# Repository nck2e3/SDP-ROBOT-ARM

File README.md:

# Face Tracking Robotic Arm

## Overview

This repository documents a Senior Design Project (SDP) centered around a robotic arm system. The project features **custom-developed firmware and hardware**, built to extend and optimize the functionality of an existing mechanical design. The full technical report can be found in the `Docs/` folder of this repository. This project was developed by **Junhee Lee** and **Noah King** as part of their Senior Design Project.

> ⚠️ Note: The mechanical CAD files—except for our custom-modeled housing—are sourced directly from the original forked repository, community_robot_arm, and remain unmodified. All electronic hardware and firmware in this repository are original to this project.

| Schematic                        |
|----------------------------------|
|        |

| PCB Photo                        |
|----------------------------------|
|        |

| Custom Housing                   | Entire Assembly                  |
|----------------------------------|----------------------------------|
|      |          |

## Repository Structure

- `Firmware/` - Custom embedded firmware developed for motor control, sensing, and task coordination.
- `Hardware/` - Custom PCB schematics and layouts designed to interface with the robotic arm and support sensors and actuators.
- `Mechanical_Design/` - Original CAD files sourced from the forked project (see Acknowledgments).
- `Documentation/` - Design notes, test procedures, and system configuration details.

## Key Features

- Custom PCB design utilizing TMC-2209 motor drivers and an STM-32 microcontroller
- Face detection and tracking via external vision processing pipeline

## Acknowledgments

All firmware, hardware integration, and system-level enhancements were designed and implemented by the team.

Mechanical design elements, including all CAD files, originate from the [community_robot_arm](https://github.com/20sffactory/community_robot_arm) repository. These files were used unmodified and served as the foundation for the custom developments described in this repository.

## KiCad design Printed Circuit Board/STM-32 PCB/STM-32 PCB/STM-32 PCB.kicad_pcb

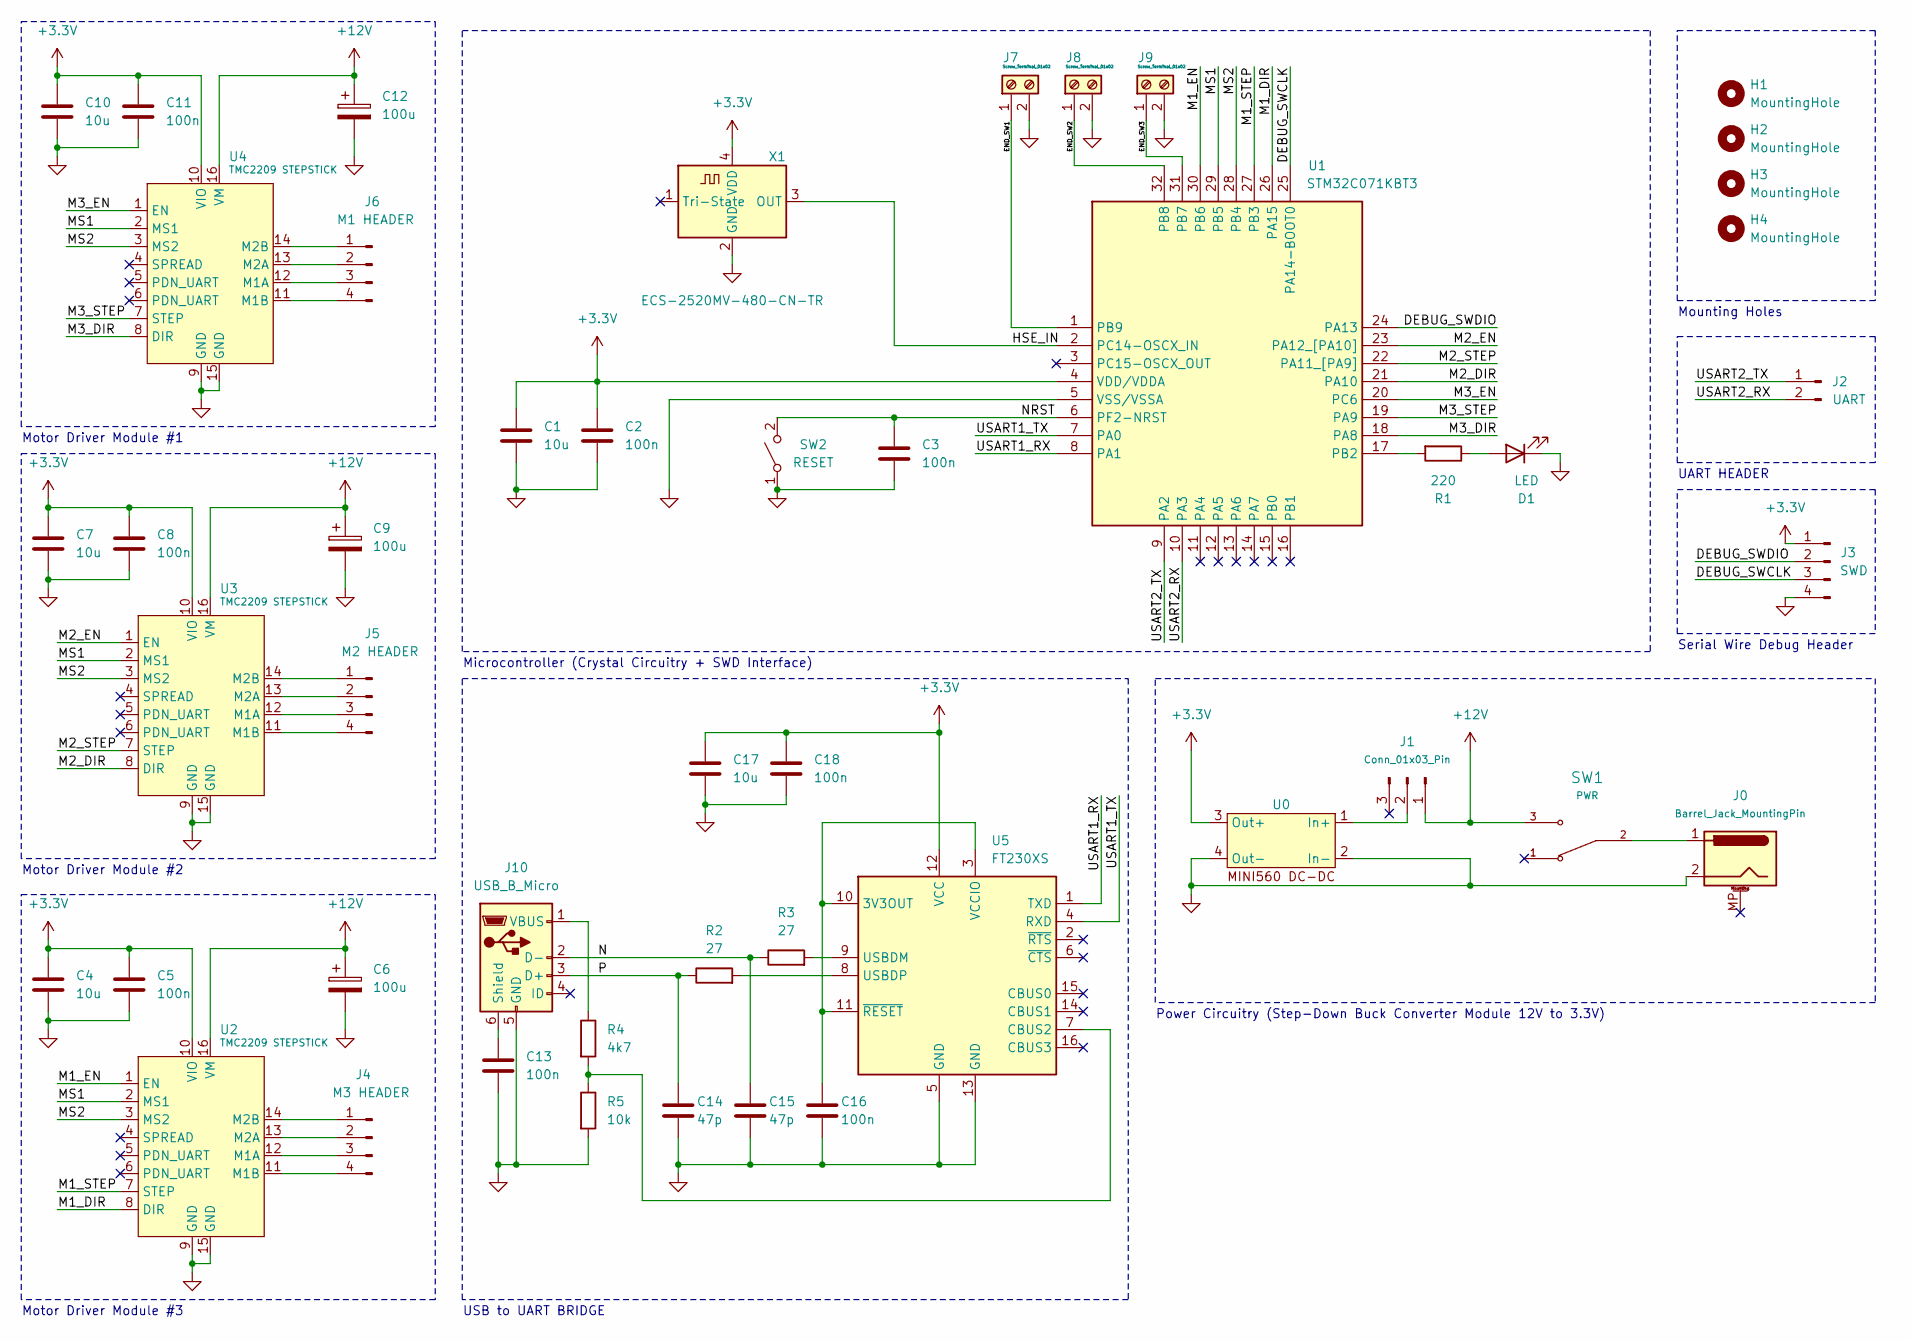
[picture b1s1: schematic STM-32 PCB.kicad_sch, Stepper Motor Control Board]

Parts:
C1, C4, C7, C10, C17: 10u; C_1206_3216Metric_Pad1.33x1.80mm_HandSolder
C2, C3, C5, C8, C11, C13, C16, C18: 100n; C_0603_1608Metric
C6, C9, C12: 100u; 50YXJ100MT78X11.5
C14, C15: 47p; C_0603_1608Metric
D1: LED; LED_1206_3216Metric
H1, H2, H3, H4: MountingHole; MountingHole_3.2mm_M3
J0: Barrel_Jack_MountingPin; BarrelJack_Horizontal
J1: Conn_01x03_Pin; PinHeader_1x03_P2.54mm_Vertical
J2: UART; PinHeader_1x02_P2.54mm_Vertical
J3: SWD; PinHeader_1x04_P2.54mm_Vertical
J4: M3 HEADER; PinHeader_1x04_P2.54mm_Vertical
J5: M2 HEADER; PinHeader_1x04_P2.54mm_Vertical
J6: M1 HEADER; PinHeader_1x04_P2.54mm_Vertical
J7, J8, J9: Screw_Terminal_01x02; TerminalBlock_Phoenix_MPT-0,5-2-2.54_1x02_P2.54mm_Horizontal
J10: USB_B_Micro; USB_Micro-B_Amphenol_10118193-0001LF_Horizontal
R1: 220; R_0603_1608Metric
R2, R3: 27; R_0603_1608Metric
R4: 4k7; R_0603_1608Metric
R5: 10k; R_0603_1608Metric
SW1: PWR; SW_500SSP1S1M6QEA; PARTREV D
SW2: RESET; SW_TH_Tactile_Omron_B3F-10xx
U0: MINI-560 DC-DC; MINI-560
U1: STM32C071KBT3; QFP80P900X900X160-32N; Manufacturer_Part_Number STM32C071KBT3
U2, U3, U4: TMC2209 STEPSTICK; TMC-2209_Stepstick
U5: FT230XS; SSOP-16_3.9x4.9mm_P0.635mm
X1: ECS-2520MV-480-CN-TR; Oscillator_SMD_ECS_2520MV-xxx-xx-4Pin_2.5x2.0mm

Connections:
+3.3V: C1.1, C2.1, C4.1, C5.1, C7.1, C8.1, C10.1, C11.1, C17.1, C18.1, J3.1, U0.3 (Out+), U1.4 (VDD/VDDA), U2.10 (VIO), U3.10 (VIO), U4.10 (VIO), U5.12 (VCC), X1.4 (VDD)
+12V: C6.1, C9.1, C12.1, J1.1, SW1.3, U2.16 (VM), U3.16 (VM), U4.16 (VM)
/DEBUG_SWCLK: J3.3, U1.25 (PA14-BOOT0)
/DEBUG_SWDIO: J3.2, U1.24 (PA13)
/END_SW1: J7.1, U1.1 (PB9)
/END_SW2: J8.1, U1.32 (PB8)
/END_SW3: J9.1, U1.31 (PB7)
/HSE_IN: U1.2 (PC14-OSCX_IN), X1.3 (OUT)
/M1_DIR: U1.26 (PA15), U2.8 (DIR)
/M1_EN: U1.30 (PB6), U2.1 (EN)
/M1_STEP: U1.27 (PB3), U2.7 (STEP)
/M2_DIR: U1.21 (PA10), U3.8 (DIR)
/M2_EN: U1.23 (PA12_[PA10]), U3.1 (EN)
/M2_STEP: U1.22 (PA11_[PA9]), U3.7 (STEP)
/M3_DIR: U1.18 (PA8), U4.8 (DIR)
/M3_EN: U1.20 (PC6), U4.1 (EN)
/M3_STEP: U1.19 (PA9), U4.7 (STEP)
/MS1: U1.29 (PB5), U2.2 (MS1), U3.2 (MS1), U4.2 (MS1)
/MS2: U1.28 (PB4), U2.3 (MS2), U3.3 (MS2), U4.3 (MS2)
/N: C15.1, J10.2 (D-), R3.1
/NRST: C3.1, SW2.2 (B), U1.6 (PF2-NRST)
/P: C14.1, J10.3 (D+), R2.1
/USART1_RX: U1.8 (PA1), U5.1 (TXD)
/USART1_TX: U1.7 (PA0), U5.4 (RXD)
/USART2_RX: J2.2, U1.10 (PA3)
/USART2_TX: J2.1, U1.9 (PA2)
GND: C1.2, C2.2, C3.2, C4.2, C5.2, C6.2, C7.2, C8.2, C9.2, C10.2, C11.2, C12.2, C13.2, C14.2, C15.2, C16.2, C17.2, C18.2, D1.1 (K), J0.2, J3.4, J7.2, J8.2, J9.2, J10.5 (GND), R5.2, SW2.1 (A), U0.2 (In-), U0.4 (Out-), U1.5 (VSS/VSSA), U2.9 (GND), U2.15 (GND), U3.9 (GND), U3.15 (GND), U4.9 (GND), U4.15 (GND), U5.5 (GND), U5.13 (GND), X1.2 (GND)
unnamed: D1.2 (A), R1.1
unnamed: J0.1, SW1.2
unnamed: J1.2, U0.1 (In+)
unnamed: J4.1, U2.14 (M2B)
unnamed: J4.2, U2.13 (M2A)
unnamed: J4.3, U2.12 (M1A)
unnamed: J4.4, U2.11 (M1B)
unnamed: J5.1, U3.14 (M2B)
unnamed: J5.2, U3.13 (M2A)
unnamed: J5.3, U3.12 (M1A)
unnamed: J5.4, U3.11 (M1B)
unnamed: J6.1, U4.14 (M2B)
unnamed: J6.2, U4.13 (M2A)
unnamed: J6.3, U4.12 (M1A)
unnamed: J6.4, U4.11 (M1B)
unnamed: C13.1, J10.6 (Shield)
unnamed: J10.1 (VBUS), R4.1
unnamed: R1.2, U1.17 (PB2)
unnamed: C16.1, U5.3 (VCCIO), U5.10 (3V3OUT), U5.11 (~RESET)
unnamed: R4.2, R5.1, U5.7 (CBUS2)
unnamed: R3.2, U5.9 (USBDM)
unnamed: R2.2, U5.8 (USBDP)

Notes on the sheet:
Motor Driver Module #2
UART HEADER
Serial Wire Debug Header
Motor Driver Module #1
Power Circuitry (Step-Down Buck Converter Module 12V to 3.3V)
USB to UART BRIDGE
Mounting Holes
Microcontroller (Crystal Circuitry + SWD Interface)
Motor Driver Module #3

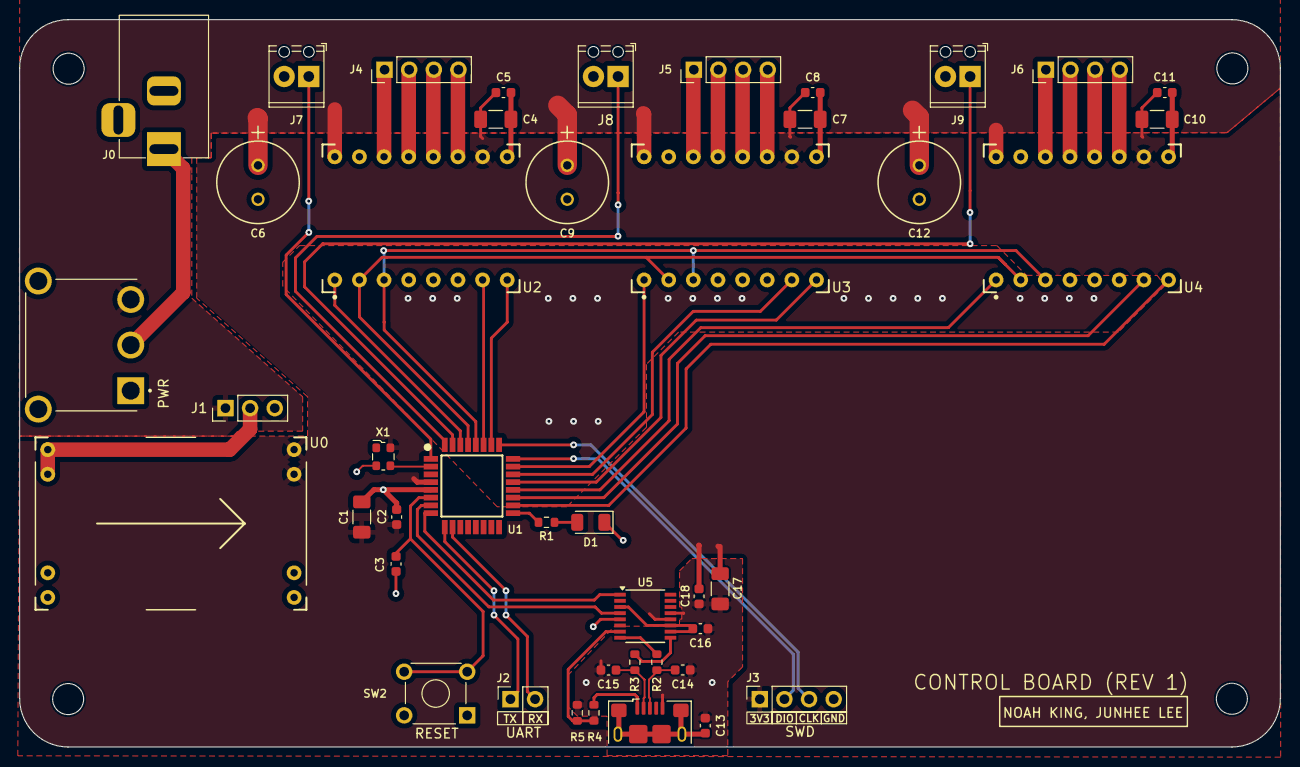
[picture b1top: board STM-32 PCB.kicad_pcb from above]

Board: 2 copper layers, 130.0 x 75.0 mm, 48 parts (0 on the bottom side), 49 nets.

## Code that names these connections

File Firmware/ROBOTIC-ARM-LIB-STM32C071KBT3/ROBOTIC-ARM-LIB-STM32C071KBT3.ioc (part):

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Mcu.Name=STM32C071KBTx
Mcu.Package=LQFP32_GP
Mcu.UserName=STM32C071KBTx
PA0.Mode=Asynchronous
PA0.Signal=USART1_TX
PA1.Mode=Asynchronous
PA1.Signal=USART1_RX
PA10\ [PA12].Signal=GPIO_Output
PA11\ [PA9].Signal=GPIO_Output
PA12\ [PA10].Signal=GPIO_Output
PA13.Mode=Serial_Wire
PA13.Signal=DEBUG_SWDIO
PA14-BOOT0.Mode=Serial_Wire
PA14-BOOT0.Signal=DEBUG_SWCLK
PA15.Signal=GPIO_Output
PA2.Mode=Asynchronous
PA2.Signal=USART2_TX
PA3.Mode=Asynchronous
PA3.Signal=USART2_RX
PA8.Signal=GPIO_Output
PA9\ [PA11].Signal=GPIO_Output
PB2.Signal=GPIO_Output
PB3.Signal=GPIO_Output
PB4.Signal=GPIO_Output
PB5.Signal=GPIO_Output
PB6.Signal=GPIO_Output
PB7.GPIOParameters=GPIO_PuPd
PB7.GPIO_PuPd=GPIO_PULLUP
PB7.Signal=GPIO_Input
PB8.GPIOParameters=GPIO_PuPd
PB8.GPIO_PuPd=GPIO_PULLUP
PB8.Signal=GPIO_Input
PB9.GPIOParameters=GPIO_PuPd
PB9.GPIO_PuPd=GPIO_PULLUP
PB9.Signal=GPIO_Input
PC14-OSCX_IN(PC14).Mode=HSE-External-Clock-Source
PC14-OSCX_IN(PC14).Signal=RCC_OSCX_IN
PC6.Signal=GPIO_Output
RCC.HSE_VALUE=48000000
RCC.SYSCLKFreq_VALUE=48000000
RCC.SYSCLKSource=RCC_SYSCLKSOURCE_HSIUSB48
board=custom

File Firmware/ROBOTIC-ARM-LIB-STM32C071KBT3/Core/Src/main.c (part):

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  /* USER CODE BEGIN 2 */
  HAL_TIM_Base_Start(&htim1);
  stepper_init(&M1_DRIVER,
			   M1_EN_PORT, M1_EN_PIN,
		       GLOBAL_MS1_PORT, GLOBAL_MS1_PIN,
			   GLOBAL_MS2_PORT, GLOBAL_MS2_PIN,
			   M1_STEP_PORT, M1_STEP_PIN,
			   M1_DIR_PORT, M1_DIR_PIN,
		       M2_ENDSTOP_PORT, M2_ENDSTOP_PIN);
  stepper_init(&M2_DRIVER,
		   	   M2_EN_PORT, M2_EN_PIN,
			   GLOBAL_MS1_PORT, GLOBAL_MS1_PIN,
			   GLOBAL_MS2_PORT, GLOBAL_MS2_PIN,
			   M2_STEP_PORT, M2_STEP_PIN,
			   M2_DIR_PORT, M2_DIR_PIN,
			   M2_ENDSTOP_PORT, M2_ENDSTOP_PIN);
  stepper_init(&M3_DRIVER,
		       M3_EN_PORT, M3_EN_PIN,
		       GLOBAL_MS1_PORT, GLOBAL_MS1_PIN,
		       GLOBAL_MS2_PORT, GLOBAL_MS2_PIN,
		       M3_STEP_PORT, M3_STEP_PIN,
		       M3_DIR_PORT, M3_DIR_PIN,
		       M3_ENDSTOP_PORT, M3_ENDSTOP_PIN);

  const char debug_msg[] = "STARTING UP!!!\n";
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  /*Configure GPIO pin Output Level */
  HAL_GPIO_WritePin(GPIOC, GPIO_PIN_6, GPIO_PIN_RESET);

  /*Configure GPIO pins : PB9 PB7 PB8 */
  GPIO_InitStruct.Pin = GPIO_PIN_9|GPIO_PIN_7|GPIO_PIN_8;
  GPIO_InitStruct.Mode = GPIO_MODE_INPUT;
  GPIO_InitStruct.Pull = GPIO_PULLUP;
  HAL_GPIO_Init(GPIOB, &GPIO_InitStruct);

  /*Configure GPIO pins : PB2 PB3 PB4 PB5
                           PB6 */
  GPIO_InitStruct.Pin = GPIO_PIN_2|GPIO_PIN_3|GPIO_PIN_4|GPIO_PIN_5
                          |GPIO_PIN_6;
  GPIO_InitStruct.Mode = GPIO_MODE_OUTPUT_PP;
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  GPIO_InitStruct.Speed = GPIO_SPEED_FREQ_LOW;
  HAL_GPIO_Init(GPIOB, &GPIO_InitStruct);

  /*Configure GPIO pins : PA8 PA9 PA10 PA11
                           PA12 PA15 */
  GPIO_InitStruct.Pin = GPIO_PIN_8|GPIO_PIN_9|GPIO_PIN_10|GPIO_PIN_11
                          |GPIO_PIN_12|GPIO_PIN_15;
  GPIO_InitStruct.Mode = GPIO_MODE_OUTPUT_PP;
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  GPIO_InitStruct.Speed = GPIO_SPEED_FREQ_LOW;
  HAL_GPIO_Init(GPIOA, &GPIO_InitStruct);

  /*Configure GPIO pin : PC6 */
  GPIO_InitStruct.Pin = GPIO_PIN_6;
  GPIO_InitStruct.Mode = GPIO_MODE_OUTPUT_PP;
  GPIO_InitStruct.Pull = GPIO_NOPULL;
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
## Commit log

2025-05-01 Removed firmware folders...
2025-05-01 Added custom firmware, added PCB files, added software, removed arduino firmware...
2025-05-01 Skeleton documentation...
2025-05-01 Updated documentation...
2025-05-27 Added images and more docs...
2025-05-27 Added more images and updated documentation...
2025-05-27 Updated directory structure...

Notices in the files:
Firmware/ROBOTIC-ARM-LIB-STM32C071KBT3/Core/Src/main.c:
Copyright (c) 2025 STMicroelectronics.
All rights reserved.
This software is licensed under terms that can be found in the LICENSE file
parts and their libraries:
Copyright 2016 Accelerated Designs. All rights reserved.
